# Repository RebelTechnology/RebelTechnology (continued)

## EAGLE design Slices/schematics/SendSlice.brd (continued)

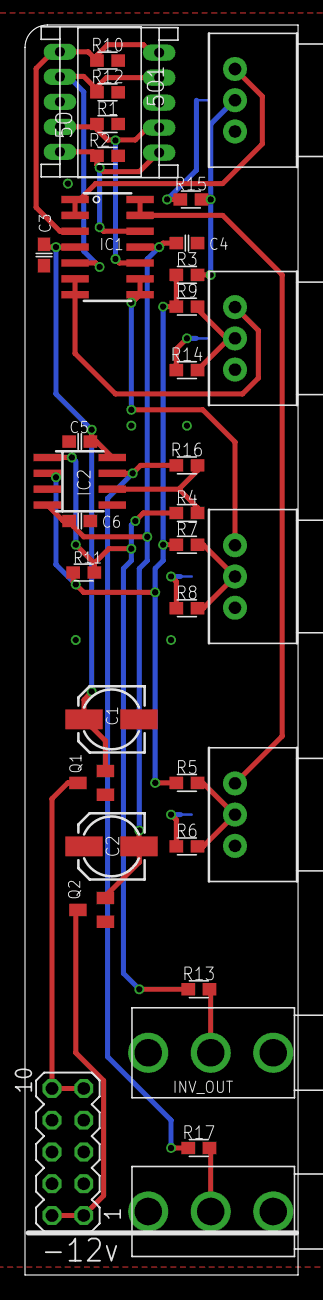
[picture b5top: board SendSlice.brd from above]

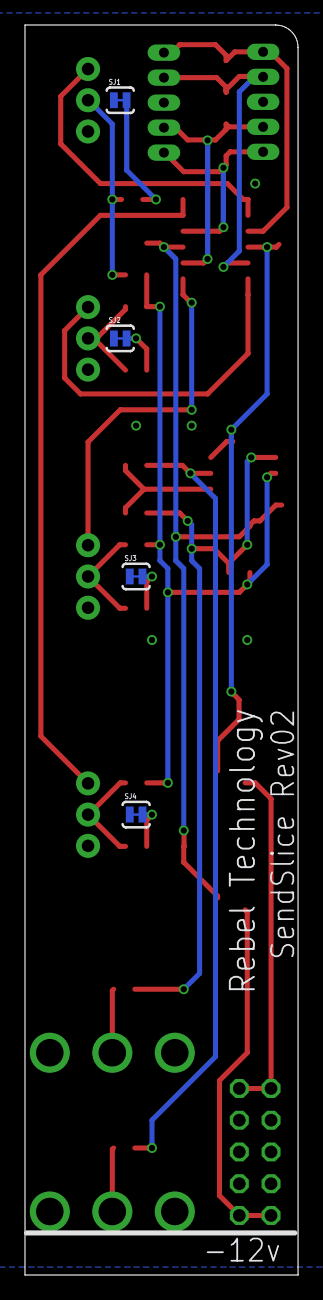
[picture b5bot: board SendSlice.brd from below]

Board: 2 copper layers, 21.8 x 100.0 mm, 40 parts (4 on the bottom side), 27 nets.

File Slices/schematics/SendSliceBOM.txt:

Partlist exported from C:/cygwin64/home/padski/RebelTechnology/Slices/schematics/SendSlice.sch at 17/01/2017 14:56

Qty Value             Device             Package           Parts                   Description                          
1                     MA05-2             MA05-2            SV1                     PIN HEADER                           
4   100n              C-EUC0603          C0603             C3, C4, C5, C6          CAPACITOR, European symbol           
6   10k               R-EU_0603          0603              R3, R4, R5, R7, R9, R16 RESISTOR, European symbol            
4   10k lin           POT-BOURNS-PTD901  POT-BOURNS-PTD901 U$1, U$2, U$3, U$4                                           
2   10u               CPOL-EU153CLV-0505 153CLV-0505       C1, C2                  POLARIZED CAPACITOR, European symbol 
4   1M                R-EU_0603          0603              R1, R2, R10, R12        RESISTOR, European symbol            
2   1k                R-EU_0603          0603              R13, R17                RESISTOR, European symbol            
1   20k               R-EU_0603          0603              R11                     RESISTOR, European symbol            
4   2k7               R-EU_0603          0603              R6, R8, R14, R15        RESISTOR, European symbol            
1   BSS123            BSS123             SOT23             Q2                      N-CHANNEL MOS FET                    
2   CON-JST_PH_5W     CON-JST_PH_5W      CON-JST_PH_5W     5O, 5O1                                                      
2   JACK-UJ-3502-R    JACK-UJ-3502-R     UJ-3502-R         INV_OUT, OUT                                                 
1   QUAD_OPAMPD       QUAD_OPAMPD        SO14              IC1                     OP AMP                               
1   SI2309CDS         BSS84              SOT23             Q1                      P-CHANNEL MOS FET                    
4   SOLDERJUMPERTRACE SOLDERJUMPERTRACE  SJ_2S-TRACE       SJ1, SJ2, SJ3, SJ4      Solder Jumper                        
1   TL072D            TL072D             SO08              IC2                     OP AMP

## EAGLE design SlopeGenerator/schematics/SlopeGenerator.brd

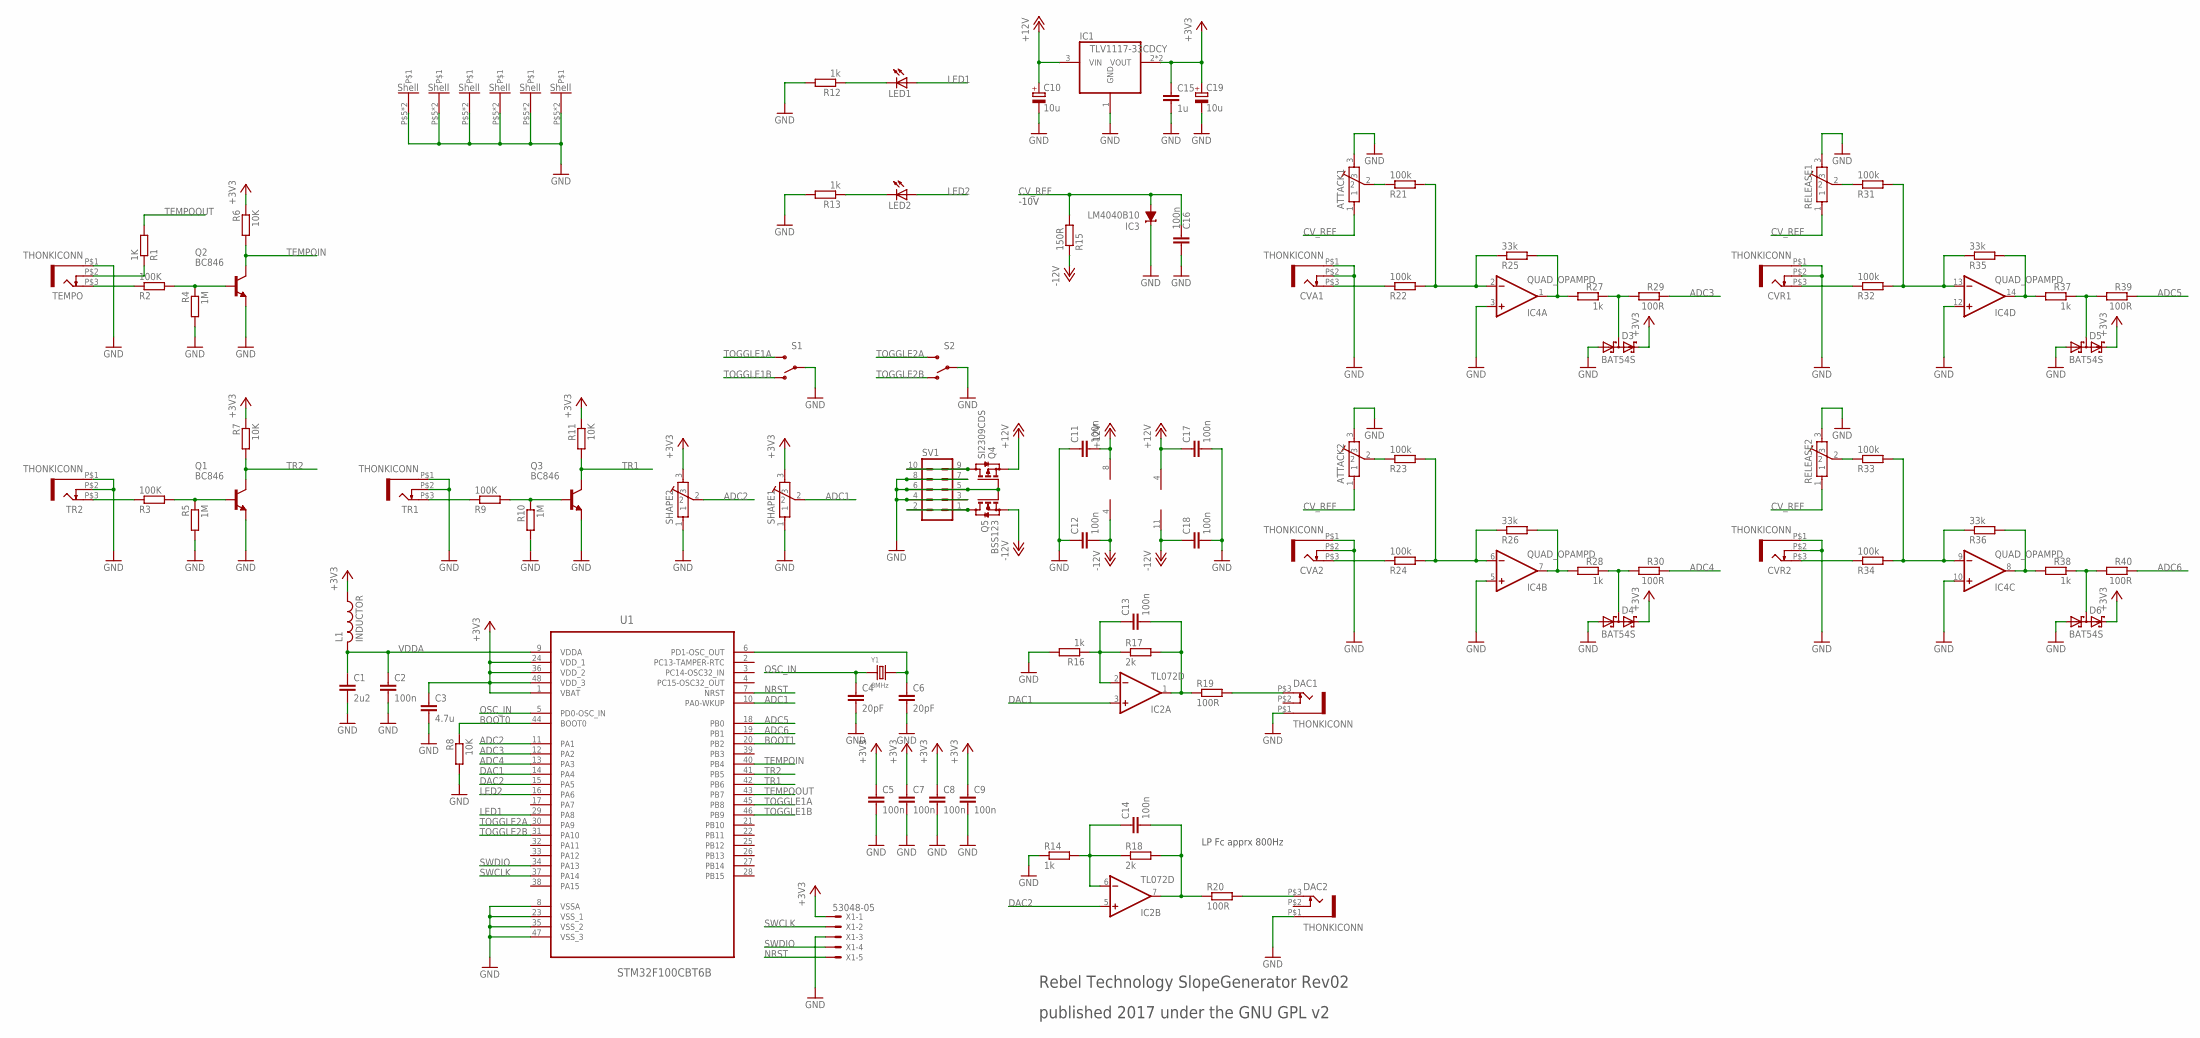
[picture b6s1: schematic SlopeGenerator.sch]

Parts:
ATTACK1, ATTACK2: POT-ALPS-RK09L1140
C1: 2u2; C0603
C2, C5, C7, C8, C9, C11, C12, C13, C14, C16, C17, C18: 100n; C0603
C3: 4.7u; C0603
C4, C6: 20pF; C0603
C10, C19: 10u; 153CLV-0405; FARNELL 882-3014
C15: 1u; C0603
CVA1, CVA2: THONKICONN
CVR1, CVR2: THONKICONN
D3, D4, D5, D6: BAT54S; SOT23
DAC1, DAC2: THONKICONN
IC1: TLV1117-33CDCY; SOT223; FARNELL 149-4942
IC2: TL072D; SO08
IC3: LM4040B10; DBZ_R-PDSO-G3
IC4: QUAD_OPAMPD; SO14
L1: INDUCTOR; 0603
LED1, LED2: LED3MM
Q1, Q2, Q3: BC846; SOT23
Q4: SI2309CDS; SOT23
Q5: BSS123; SOT23
R1: 1K; 0603
R2, R3, R9: 100K; 0603
R4, R5, R10: 1M; 0603
R6, R7, R8, R11: 10K; 0603
R12, R13, R14, R16, R27, R28, R37, R38: 1k; 0603
R15: 150R; 0603
R17, R18: 2k; 0603
R19, R20, R29, R30, R39, R40: 100R; 0603
R21, R22, R23, R24, R31, R32, R33, R34: 100k; 0603
R25, R26, R35, R36: 33k; 0603
RELEASE1, RELEASE2: POT-ALPS-RK09L1140
S1, S2: SWITCH-SPST; SWITCH-SPDT-SALECOM-T8014
SHAPE1, SHAPE2: POT-ALPS-RK09L1140
SV1: MA05-2
TEMPO: THONKICONN
TR1, TR2: THONKICONN
U1: STM32F100CBT6B; QFP50P900X900X160-48N
X1: 53048-05
Y1: 8MHz; X2-SMD-5.0X3.2X1.3MM

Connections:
+3V3: C3.1, C5.1, C7.1, C8.1, C9.1, C15.1, C19.+, D3.2 (C2), D4.2 (C2), D5.2 (C2), D6.2 (C2), IC1.2 (VOUT), IC1.4 (VOUT), L1.1, R6.1, R7.1, R11.1, SHAPE1.3, SHAPE2.3, U1.1 (VBAT), U1.24 (VDD_1), U1.36 (VDD_2), U1.48 (VDD_3), X1.1
+12V: C10.+, C11.2, C17.1, IC1.3 (VIN), IC2.8 (V+), IC4.4 (V+), Q4.2 (S)
-12V: C12.2, C18.1, IC2.4 (V-), IC4.11 (V-), Q5.2 (S), R15.1
ADC1: SHAPE1.2, U1.10 (PA0-WKUP)
ADC2: SHAPE2.2, U1.11 (PA1)
ADC3: R29.1, U1.12 (PA2)
ADC4: R30.1, U1.13 (PA3)
ADC5: R39.1, U1.18 (PB0)
ADC6: R40.1, U1.19 (PB1)
BOOT0: R8.1, U1.44 (BOOT0)
BOOT1: U1.20 (PB2)
CV_REF: ATTACK1.1, ATTACK2.1, C16.1, IC3.2 (A), R15.2, RELEASE1.1, RELEASE2.1
DAC1: IC2.3 (+IN), U1.14 (PA4)
DAC2: IC2.5 (+IN), U1.15 (PA5)
GND: ATTACK1.3, ATTACK1.P$5, ATTACK1.P$6, ATTACK2.3, ATTACK2.P$5, ATTACK2.P$6, C1.2, C2.2, C3.2, C4.2, C5.2, C6.2, C7.2, C8.2, C9.2, C10.-, C11.1, C12.1, C15.2, C16.2, C17.2, C18.2, C19.-, CVA1.P$1 (5), CVA1.P$2 (4), CVA2.P$1 (5), CVA2.P$2 (4), CVR1.P$1 (5), CVR1.P$2 (4), CVR2.P$1 (5), CVR2.P$2 (4), D3.1 (A1), D4.1 (A1), D5.1 (A1), D6.1 (A1), DAC1.P$1 (5), DAC2.P$1 (5), IC1.1 (GND), IC3.1 (C), IC4.3 (+IN), IC4.5 (+IN), IC4.10 (+IN), IC4.12 (+IN), Q1.2 (E), Q2.2 (E), Q3.2 (E), Q4.1 (G), Q5.1 (G), R4.2, R5.2, R8.2, R10.2, R12.2, R13.2, R14.1, R16.2, RELEASE1.3, RELEASE1.P$5, RELEASE1.P$6, RELEASE2.3, RELEASE2.P$5, RELEASE2.P$6, S1.2, S2.2, SHAPE1.1, SHAPE1.P$5, SHAPE1.P$6, SHAPE2.1, SHAPE2.P$5, SHAPE2.P$6, SV1.3, SV1.4, SV1.5, SV1.6, SV1.7, SV1.8, TEMPO.P$1 (5), TR1.P$1 (5), TR1.P$2 (4), TR2.P$1 (5), TR2.P$2 (4), U1.8 (VSSA), U1.23 (VSS_1), U1.35 (VSS_2), U1.47 (VSS_3), X1.3
LED1: LED1.A, U1.29 (PA8)
LED2: LED2.A, U1.16 (PA6)
unnamed: C6.1, U1.6 (PD1-OSC_OUT), Y1.2
unnamed: LED2.K (C), R13.1
unnamed: C14.2, IC2.7 (OUT), R18.2, R20.1
unnamed: C14.1, IC2.6 (-IN), R14.2, R18.1
unnamed: Q4.3 (D), SV1.9, SV1.10
unnamed: C13.2, IC2.1 (OUT), R17.2, R19.1
unnamed: LED1.K (C), R12.1
unnamed: Q1.1 (B), R3.2, R5.1
unnamed: Q2.1 (B), R2.2, R4.1
unnamed: R2.1, TEMPO.P$3 (3)
unnamed: C13.1, IC2.2 (-IN), R16.1, R17.1
unnamed: R3.1, TR2.P$3 (3)
unnamed: Q5.3 (D), SV1.1, SV1.2
unnamed: R1.1, TEMPO.P$2 (4)
unnamed: CVA1.P$3 (3), R22.1
unnamed: IC4.2 (-IN), R21.2, R22.2, R25.1
unnamed: ATTACK1.2, R21.1
unnamed: IC4.1 (OUT), R25.2, R27.2
unnamed: R9.1, TR1.P$3 (3)
unnamed: D3.3 (C1A2), R27.1, R29.2
unnamed: CVA2.P$3 (3), R24.1
unnamed: IC4.6 (-IN), R23.2, R24.2, R26.1
unnamed: Q3.1 (B), R9.2, R10.1
unnamed: ATTACK2.2, R23.1
unnamed: IC4.7 (OUT), R26.2, R28.2
unnamed: DAC1.P$3 (3), R19.2
unnamed: DAC2.P$3 (3), R20.2
unnamed: D4.3 (C1A2), R28.1, R30.2
unnamed: CVR1.P$3 (3), R32.1
unnamed: IC4.13 (-IN), R31.2, R32.2, R35.1
unnamed: R31.1, RELEASE1.2
unnamed: IC4.14 (OUT), R35.2, R37.2
unnamed: D5.3 (C1A2), R37.1, R39.2
unnamed: CVR2.P$3 (3), R34.1
unnamed: IC4.9 (-IN), R33.2, R34.2, R36.1
unnamed: R33.1, RELEASE2.2
unnamed: IC4.8 (OUT), R36.2, R38.2
unnamed: D6.3 (C1A2), R38.1, R40.2
NRST: U1.7 (NRST), X1.5
OSC_IN: C4.1, U1.5 (PD0-OSC_IN), Y1.1
SWCLK: U1.37 (PA14), X1.2
SWDIO: U1.34 (PA13), X1.4
TEMPOIN: Q2.3 (C), R6.2, U1.40 (PB4)
TEMPOOUT: R1.2, U1.43 (PB7)
TOGGLE1A: S1.3 (S), U1.45 (PB8)
TOGGLE1B: S1.1 (O), U1.46 (PB9)
TOGGLE2A: S2.3 (S), U1.30 (PA9)
TOGGLE2B: S2.1 (O), U1.31 (PA10)
TR1: Q3.3 (C), R11.2, U1.42 (PB6)
TR2: Q1.3 (C), R7.2, U1.41 (PB5)
VDDA: C1.1, C2.1, L1.2, U1.9 (VDDA)

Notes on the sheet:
Rebel Technology SlopeGenerator Rev02
published 2017 under the GNU GPL v2
LP Fc apprx 800Hz
-10V

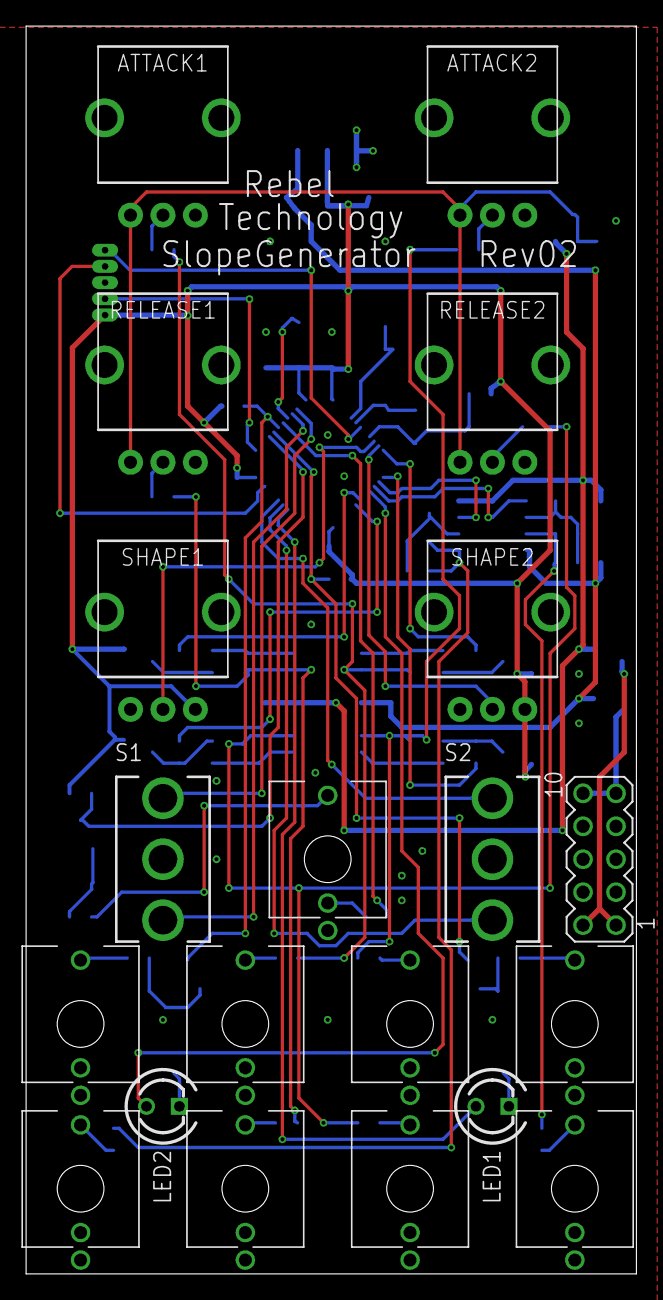
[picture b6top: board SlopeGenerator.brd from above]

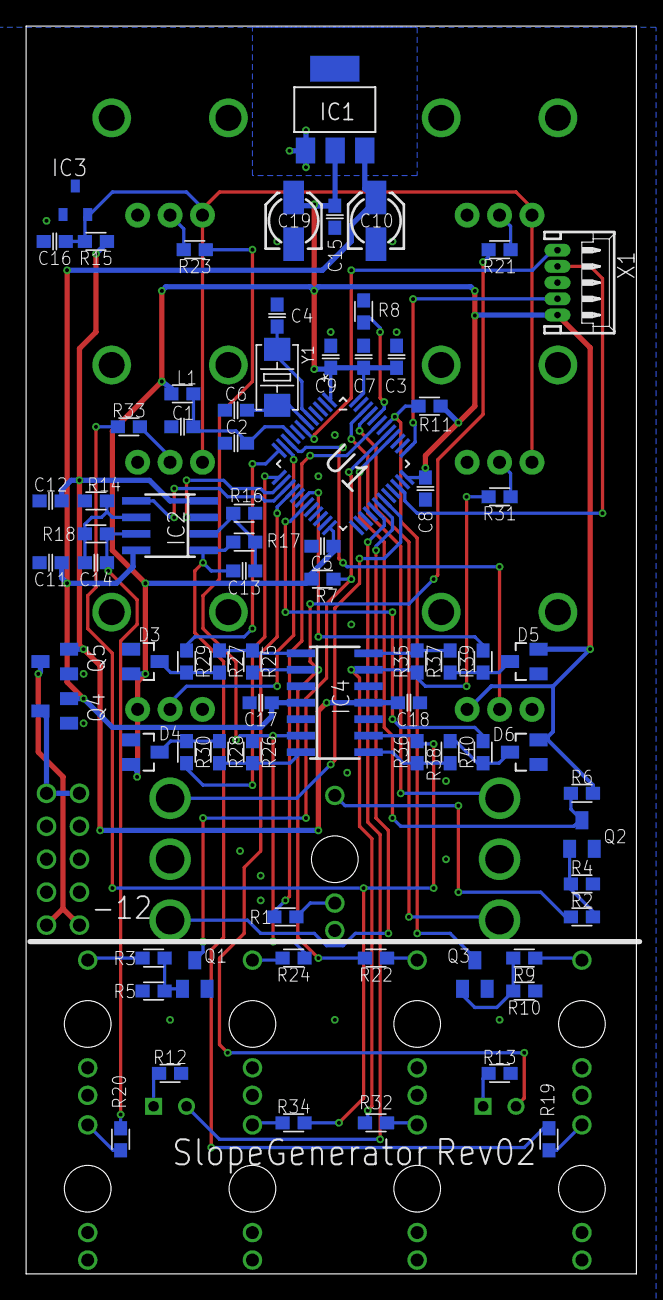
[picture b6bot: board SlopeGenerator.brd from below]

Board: 2 copper layers, 47.0 x 96.2 mm, 96 parts (76 on the bottom side), 67 nets.

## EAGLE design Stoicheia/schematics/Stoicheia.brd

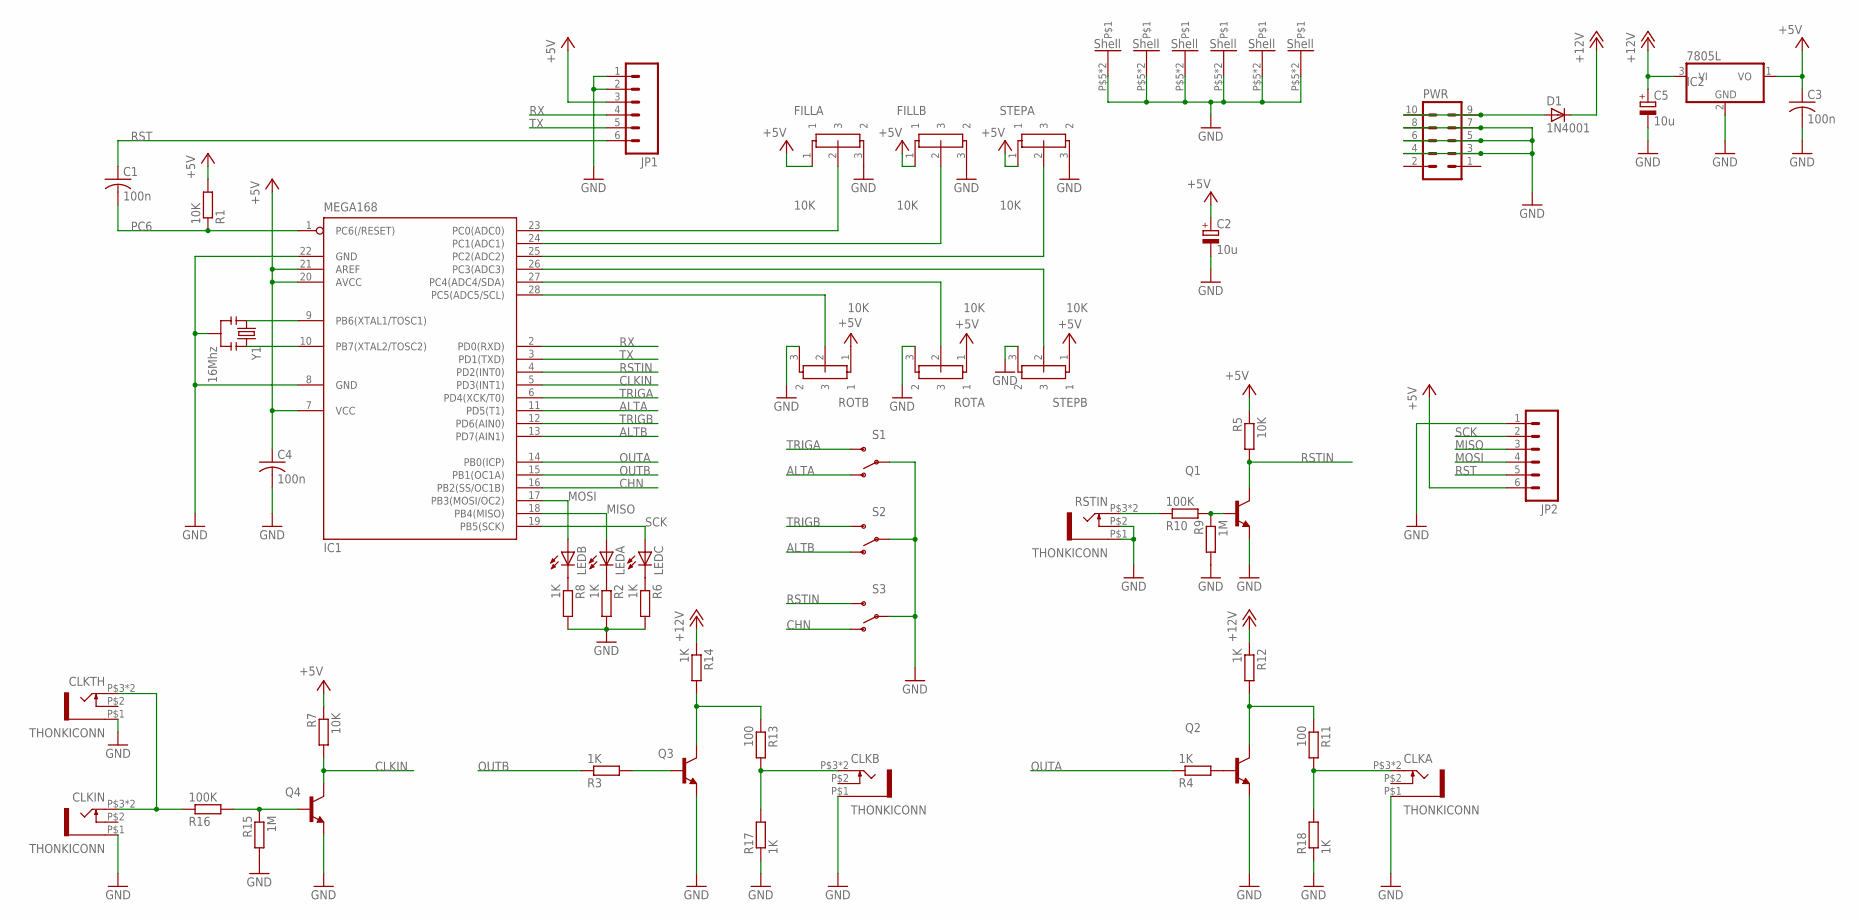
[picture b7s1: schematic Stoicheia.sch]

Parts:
C1, C3, C4: 100n; C050-024X044
C2, C5: 10u; E5-6
CLKA: THONKICONN
CLKB: THONKICONN
CLKIN: THONKICONN
CLKTH: THONKICONN
D1: 1N4001; DIODE-1N4001
FILLA: 10K; POT-ALPS-RK09L1140
FILLB: 10K; POT-ALPS-RK09L1140
IC1: MEGA168; DIL28-3
IC2: 7805L; TO92
JP1, JP2: M06SIP; 1X06
LEDA: LED3MM
LEDB: LED3MM
LEDC: LED3MM
PWR: MA05-2
Q1, Q2, Q3, Q4: 2N3904-NPN-TO92-EBC; TO92-EBC
R1, R5, R7: 10K; 0204/7
R2, R3, R4, R6, R8, R12, R14, R17, R18: 1K; 0204/7
R9, R15: 1M; 0204/7
R10, R16: 100K; 0204/7
R11, R13: 100; 0204/7
ROTA: 10K; POT-ALPS-RK09L1140
ROTB: 10K; POT-ALPS-RK09L1140
RSTIN: THONKICONN
S1, S2, S3: SWITCH-SPST; SWITCH-SPDT-SALECOM-T8014
STEPA: 10K; POT-ALPS-RK09L1140
STEPB: 10K; POT-ALPS-RK09L1140
Y1: 16Mhz; RESONATOR-PTH

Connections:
+5V: C2.+, C3.1, C4.1, FILLA.1, FILLB.1, IC1.7 (VCC), IC1.20 (AVCC), IC1.21 (AREF), IC2.1 (VO), JP1.3, JP2.6, R1.2, R5.1, R7.1, ROTA.1, ROTB.1, STEPA.1, STEPB.1
+12V: C5.+, D1.C, IC2.3 (VI), R12.1, R14.1
ALTA: IC1.11 (PD5(T1)), S1.1 (O)
ALTB: IC1.13 (PD7(AIN1)), S2.1 (O)
CHN: IC1.16 (PB2(SS/OC1B)), S3.1 (O)
CLKIN: IC1.5 (PD3(INT1)), Q4.C, R7.2
FILFB: FILLB.2 (3), IC1.24 (PC1(ADC1))
GND: C2.-, C3.2, C4.2, C5.-, CLKA.P$1 (5), CLKB.P$1 (5), CLKIN.P$1 (5), CLKTH.P$1 (5), FILLA.3 (2), FILLA.P$5, FILLA.P$6, FILLB.3 (2), FILLB.P$5, FILLB.P$6, IC1.8 (GND), IC1.22 (GND), IC2.2 (GND), JP1.1, JP1.2, JP2.1, PWR.3, PWR.4, PWR.5, PWR.6, PWR.7, PWR.8, Q1.E, Q2.E, Q3.E, Q4.E, R2.2, R6.2, R8.2, R9.2, R15.2, R17.1, R18.1, ROTA.3 (2), ROTA.P$5, ROTA.P$6, ROTB.3 (2), ROTB.P$5, ROTB.P$6, RSTIN.P$1 (5), RSTIN.P$2 (4), S1.2, S2.2, S3.2, STEPA.3 (2), STEPA.P$5, STEPA.P$6, STEPB.3 (2), STEPB.P$5, STEPB.P$6, Y1.2
MISO: IC1.18 (PB4(MISO)), JP2.3, LEDA.A
MOSI: IC1.17 (PB3(MOSI/OC2)), JP2.4, LEDB.A
unnamed: FILLA.2 (3), IC1.23 (PC0(ADC0))
unnamed: IC1.25 (PC2(ADC2)), STEPA.2 (3)
unnamed: IC1.26 (PC3(ADC3)), STEPB.2 (3)
unnamed: IC1.27 (PC4(ADC4/SDA)), ROTA.2 (3)
unnamed: IC1.28 (PC5(ADC5/SCL)), ROTB.2 (3)
unnamed: IC1.9 (PB6(XTAL1/TOSC1)), Y1.1
unnamed: IC1.10 (PB7(XTAL2/TOSC2)), Y1.3
unnamed: CLKB.P$3 (3), CLKB.P$4 (3), R13.2, R17.2
unnamed: Q3.C, R13.1, R14.2
unnamed: Q4.B, R15.1, R16.2
unnamed: CLKIN.P$3 (3), CLKIN.P$4 (3), CLKTH.P$3 (3), CLKTH.P$4 (3), R16.1
unnamed: R10.1, RSTIN.P$3 (3), RSTIN.P$4 (3)
unnamed: Q3.B, R3.2
unnamed: LEDB.K (C), R8.1
unnamed: Q2.B, R4.2
unnamed: CLKA.P$3 (3), CLKA.P$4 (3), R11.2, R18.2
unnamed: Q2.C, R11.1, R12.2
unnamed: LEDA.K (C), R2.1
unnamed: LEDC.K (C), R6.1
unnamed: Q1.B, R9.1, R10.2
unnamed: D1.A, PWR.9, PWR.10
OUTA: IC1.14 (PB0(ICP)), R4.1
OUTB: IC1.15 (PB1(OC1A)), R3.1
PC6: C1.2, IC1.1 (PC6(/RESET)), R1.1
RST: C1.1, JP1.6, JP2.5
RSTIN: IC1.4 (PD2(INT0)), Q1.C, R5.2, S3.3 (S)
RX: IC1.2 (PD0(RXD)), JP1.4
SCK: IC1.19 (PB5(SCK)), JP2.2, LEDC.A
TRIGA: IC1.6 (PD4(XCK/T0)), S1.3 (S)
TRIGB: IC1.12 (PD6(AIN0)), S2.3 (S)
TX: IC1.3 (PD1(TXD)), JP1.5

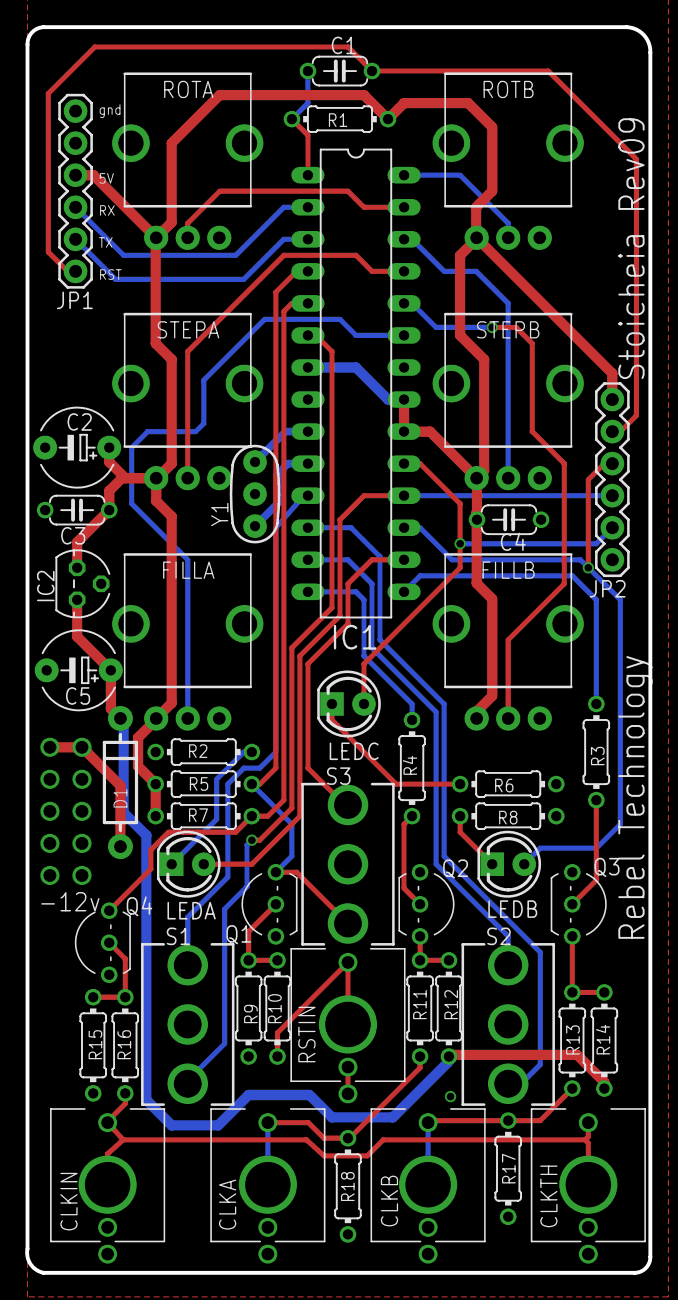
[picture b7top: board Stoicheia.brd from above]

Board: 2 copper layers, 49.4 x 98.7 mm, 51 parts (1 on the bottom side), 41 nets.
